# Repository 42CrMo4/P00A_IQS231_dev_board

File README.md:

# KiCad_Template

This is a template repo for KiCAD v6 projects with 

### Goal & Status

Goal: prototype
Status: implementation

| undefined                             | learn                                                                                            | prototype                  | 80-20-rule                                                   | polished Product |
|---------------------------------------|--------------------------------------------------------------------------------------------------|----------------------------|--------------------------------------------------------------|------------------|
| not known what the project will bring | personally learn something new (function, design, process) otherwise no usefull outcome expected | a working prototype or mvp | 80% outcome with 20% effort. Dont expect a finished product. | -                |

| idea                   | design                                                | implementation | testing | finished |
|------------------------|-------------------------------------------------------|----------------|---------|----------|
| brainstorming workflow | putting together a goal list, architecture, hig level | schematic, pcb |         |          |

## Todo

* ~add DRC, ERC as seperate WF~ 
* ~add DRC, ERC to release WF as blocking~
* ~add release checklist~
* order release checklist
* ~add workflow to automatically create new realease checklist and realease note file and reset the generic for the next release~
* ~Rename artefacts with project name and date?~
* Add diffrent PCB manufactures output via kibot
* ~Update to kicad6_auto:1.3.0~
* use version number for template

## Usage

hit "use this template" button
delet all unneded files in Doc folder
delet all Schematic stuff but not the text Placeholders <<...>>
delet all PCB stuff but not the text Placeholders <<...>> and the Board Edge (or the iBOM will fail). You can remodel it later.

### Workflow
If not working:
setting -> action -> general -> Workflow permissions -> Read and write permissions

## working

in the first workflow run the action will create a new branch "documentation" to store the newest PCBdraw pictures. 
Each action run will force push the png to this branch. So so not use the Fabrication folder in the documentation branch.

## Description. 

| Font                                                                    | Back                                                                      |
|-------------------------------------------------------------------------|---------------------------------------------------------------------------|
|  |  |

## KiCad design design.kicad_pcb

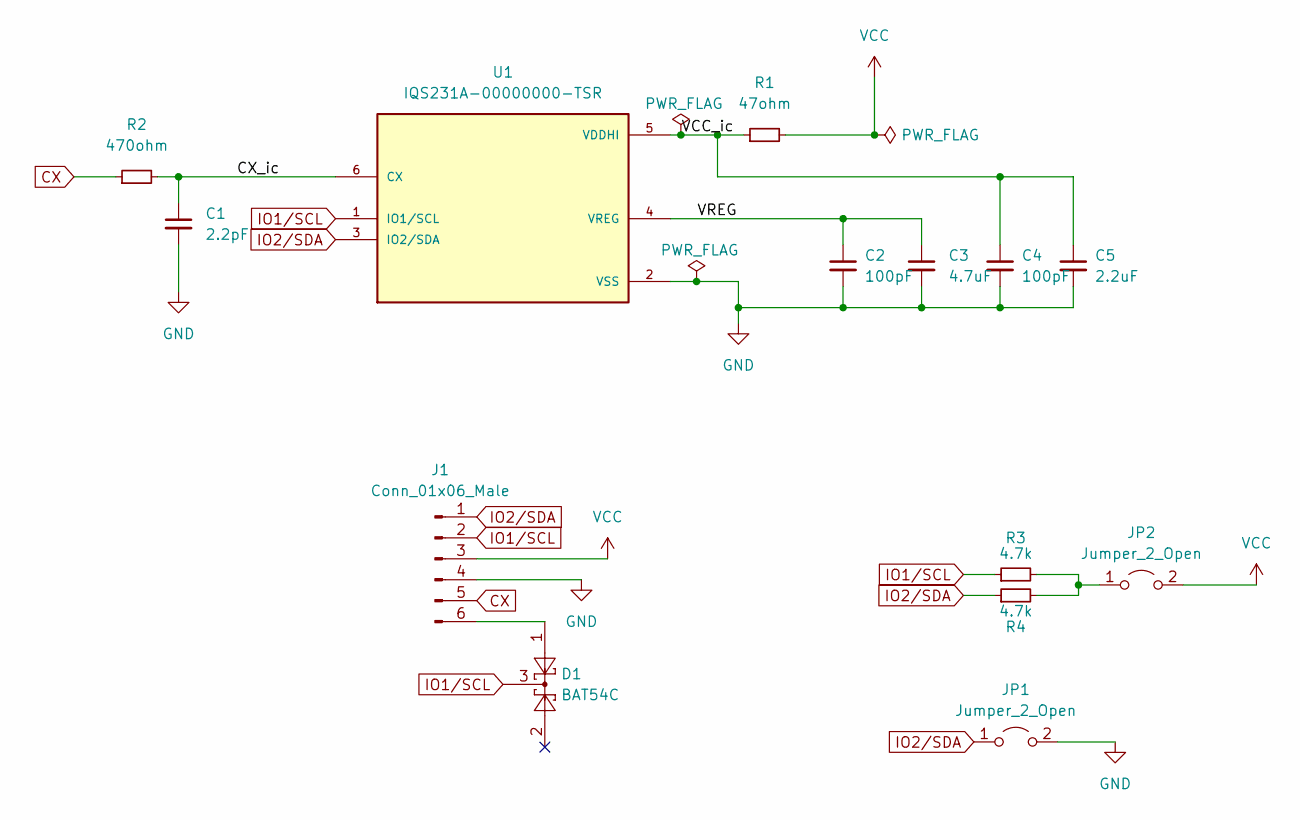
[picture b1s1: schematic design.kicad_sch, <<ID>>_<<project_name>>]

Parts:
C1: 2.2pF; C_0805_2012Metric
C2, C4: 100pF; C_0805_2012Metric
C3: 4.7uF; C_0805_2012Metric
C5: 2.2uF; C_0805_2012Metric
D1: BAT54C; SOT-23
J1: Conn_01x06_Male; PinHeader_1x06_P2.54mm_Vertical
JP1, JP2: Jumper_2_Open; PinHeader_1x02_P2.54mm_Vertical
R1: 47ohm; R_0805_2012Metric
R2: 470ohm; R_0805_2012Metric
R3, R4: 4.7k; R_0805_2012Metric
U1: IQS231A-00000000-TSR; SOT95P280X100-6N; PARTREV 2.4

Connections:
/CX_ic: C1.1, R2.2, U1.6 (CX)
/VCC_ic: C4.1, C5.1, R1.1, U1.5 (VDDHI)
/VREG: C2.1, C3.1, U1.4 (VREG)
CX: J1.5, R2.1
GND: C1.2, C2.2, C3.2, C4.2, C5.2, J1.4, JP1.2 (B), U1.2 (VSS)
IO1/SCL: D1.3, J1.2, R3.1, U1.1 (IO1/SCL)
IO2/SDA: J1.1, JP1.1 (A), R4.1, U1.3 (IO2/SDA)
unnamed: D1.1, J1.6
unnamed: JP2.1 (A), R3.2, R4.2
VCC: J1.3, JP2.2 (B), R1.2

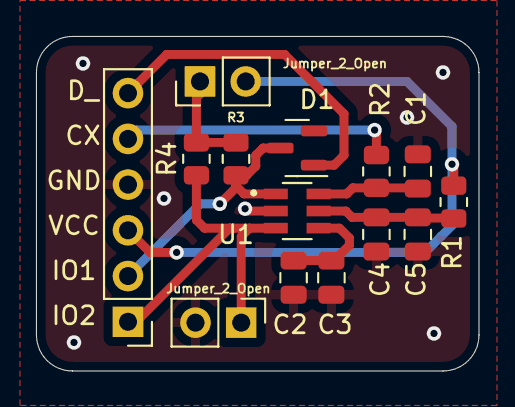
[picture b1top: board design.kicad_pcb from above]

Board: 2 copper layers, 24.6 x 18.6 mm, 14 parts (0 on the bottom side), 10 nets.

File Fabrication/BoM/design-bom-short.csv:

Row,Description,Part,References,Value,Footprint,Quantity Per PCB,Status,Datasheet,PARTREV,STANDARD,MAXIMUM_PACKAGE_HEIGHT,MANUFACTURER
1,"Unpolarized capacitor, small symbol",C_Small,C1,2.2pF,C_0805_2012Metric,1, ,~,,,,
2,"Unpolarized capacitor, small symbol",C_Small,C2 C4,100pF,C_0805_2012Metric,2, ,~,,,,
3,"Unpolarized capacitor, small symbol",C_Small,C5,2.2uF,C_0805_2012Metric,1, ,~,,,,
4,"Unpolarized capacitor, small symbol",C_Small,C3,4.7uF,C_0805_2012Metric,1, ,~,,,,
5,"dual schottky barrier diode, common cathode",BAT54C,D1,BAT54C,SOT-23,1, ,http://www.diodes.com/_files/datasheets/ds11005.pdf,,,,
6,"Generic connector, single row, 01x06, script generated (kicad-library-utils/schlib/autogen/connector/)",Conn_01x06_Male,J1,Conn_01x06_Male,PinHeader_1x06_P2.54mm_Vertical,1, ,~,,,,
7,"Jumper, 2-pole, open",Jumper_2_Open,JP1 JP2,Jumper_2_Open,PinHeader_1x02_P2.54mm_Vertical,2, ,~,,,,
8,"Resistor, small symbol",R_Small,R1,47ohm,R_0805_2012Metric,1, ,~,,,,
9,"Resistor, small symbol",R_Small,R2,470ohm,R_0805_2012Metric,1, ,~,,,,
10,"Resistor, small symbol",R_Small,R3 R4,4.7k,R_0805_2012Metric,2, ,~,,,,
11,,IQS231A-00000000-TSR,U1,IQS231A-00000000-TSR,SOT95P280X100-6N,1, ,,2.4,IPC-7351B,1mm,AZOTEQ

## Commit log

2023-11-12 set goal and status
2023-11-12 DEL all PCB stuff
2023-11-12 DEL all SCH stuff
2023-11-12 PCB add variables text block
2023-11-12 annotate and assign footprints
2023-11-12 footprint assigned correction
2023-11-13 add aisle short name
2023-11-13 change order aisler rename copy
2023-11-13 again aisler rename ordering
2023-11-13 pcb layout small sch changes for pcb
2023-11-13 add groundplane and DRC/ERC
2023-11-13 Update Bom and PCB_top
2023-11-13 DEL old files
2023-11-13 Release note und Checklist
2023-11-13 Archive & Renew release docs
2023-11-13 add aisler rename to release workflow
